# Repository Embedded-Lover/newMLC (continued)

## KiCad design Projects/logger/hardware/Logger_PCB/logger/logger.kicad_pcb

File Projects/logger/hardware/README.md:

# MLC_CAN_Logger_Hardware

## Getting started

To make it easy for you to get started with GitLab, here's a list of recommended next steps.

Already a pro? Just edit this README.md and make it your own. Want to make it easy? [Use the template at the bottom](#editing-this-readme)!

## Add your files

- [ ] [Create](https://docs.gitlab.com/ee/user/project/repository/web_editor.html#create-a-file) or [upload](https://docs.gitlab.com/ee/user/project/repository/web_editor.html#upload-a-file) files
- [ ] [Add files using the command line](https://docs.gitlab.com/ee/gitlab-basics/add-file.html#add-a-file-using-the-command-line) or push an existing Git repository with the following command:

```
cd existing_repo
git remote add origin https://git.mapnalocomotive.com/ahmadi_y/mlc_can_logger_hardware.git
git branch -M main
git push -uf origin main
```

## Integrate with your tools

- [ ] [Set up project integrations](https://git.mapnalocomotive.com/ahmadi_y/mlc_can_logger_hardware/-/settings/integrations)

## Collaborate with your team

- [ ] [Invite team members and collaborators](https://docs.gitlab.com/ee/user/project/members/)
- [ ] [Create a new merge request](https://docs.gitlab.com/ee/user/project/merge_requests/creating_merge_requests.html)
- [ ] [Automatically close issues from merge requests](https://docs.gitlab.com/ee/user/project/issues/managing_issues.html#closing-issues-automatically)
- [ ] [Enable merge request approvals](https://docs.gitlab.com/ee/user/project/merge_requests/approvals/)
- [ ] [Set auto-merge](https://docs.gitlab.com/ee/user/project/merge_requests/merge_when_pipeline_succeeds.html)

## Test and Deploy

Use the built-in continuous integration in GitLab.

- [ ] [Get started with GitLab CI/CD](https://docs.gitlab.com/ee/ci/quick_start/index.html)
- [ ] [Analyze your code for known vulnerabilities with Static Application Security Testing (SAST)](https://docs.gitlab.com/ee/user/application_security/sast/)
- [ ] [Deploy to Kubernetes, Amazon EC2, or Amazon ECS using Auto Deploy](https://docs.gitlab.com/ee/topics/autodevops/requirements.html)
- [ ] [Use pull-based deployments for improved Kubernetes management](https://docs.gitlab.com/ee/user/clusters/agent/)
- [ ] [Set up protected environments](https://docs.gitlab.com/ee/ci/environments/protected_environments.html)

***

# Editing this README

When you're ready to make this README your own, just edit this file and use the handy template below (or feel free to structure it however you want - this is just a starting point!). Thanks to [makeareadme.com](https://www.makeareadme.com/) for this template.

## Suggestions for a good README

Every project is different, so consider which of these sections apply to yours. The sections used in the template are suggestions for most open source projects. Also keep in mind that while a README can be too long and detailed, too long is better than too short. If you think your README is too long, consider utilizing another form of documentation rather than cutting out information.

## Name
Choose a self-explaining name for your project.

## Description
Let people know what your project can do specifically. Provide context and add a link to any reference visitors might be unfamiliar with. A list of Features or a Background subsection can also be added here. If there are alternatives to your project, this is a good place to list differentiating factors.

## Badges
On some READMEs, you may see small images that convey metadata, such as whether or not all the tests are passing for the project. You can use Shields to add some to your README. Many services also have instructions for adding a badge.

## Visuals
Depending on what you are making, it can be a good idea to include screenshots or even a video (you'll frequently see GIFs rather than actual videos). Tools like ttygif can help, but check out Asciinema for a more sophisticated method.

## Installation
Within a particular ecosystem, there may be a common way of installing things, such as using Yarn, NuGet, or Homebrew. However, consider the possibility that whoever is reading your README is a novice and would like more guidance. Listing specific steps helps remove ambiguity and gets people to using your project as quickly as possible. If it only runs in a specific context like a particular programming language version or operating system or has dependencies that have to be installed manually, also add a Requirements subsection.

## Usage
Use examples liberally, and show the expected output if you can. It's helpful to have inline the smallest example of usage that you can demonstrate, while providing links to more sophisticated examples if they are too long to reasonably include in the README.

## Support
Tell people where they can go to for help. It can be any combination of an issue tracker, a chat room, an email address, etc.

## Roadmap
If you have ideas for releases in the future, it is a good idea to list them in the README.

## Contributing
State if you are open to contributions and what your requirements are for accepting them.

For people who want to make changes to your project, it's helpful to have some documentation on how to get started. Perhaps there is a script that they should run or some environment variables that they need to set. Make these steps explicit. These instructions could also be useful to your future self.

You can also document commands to lint the code or run tests. These steps help to ensure high code quality and reduce the likelihood that the changes inadvertently break something. Having instructions for running tests is especially helpful if it requires external setup, such as starting a Selenium server for testing in a browser.

## Authors and acknowledgment
Show your appreciation to those who have contributed to the project.

## License
For open source projects, say how it is licensed.

## Project status
If you have run out of energy or time for your project, put a note at the top of the README saying that development has slowed down or stopped completely. Someone may choose to fork your project or volunteer to step in as a maintainer or owner, allowing your project to keep going. You can also make an explicit request for maintainers.

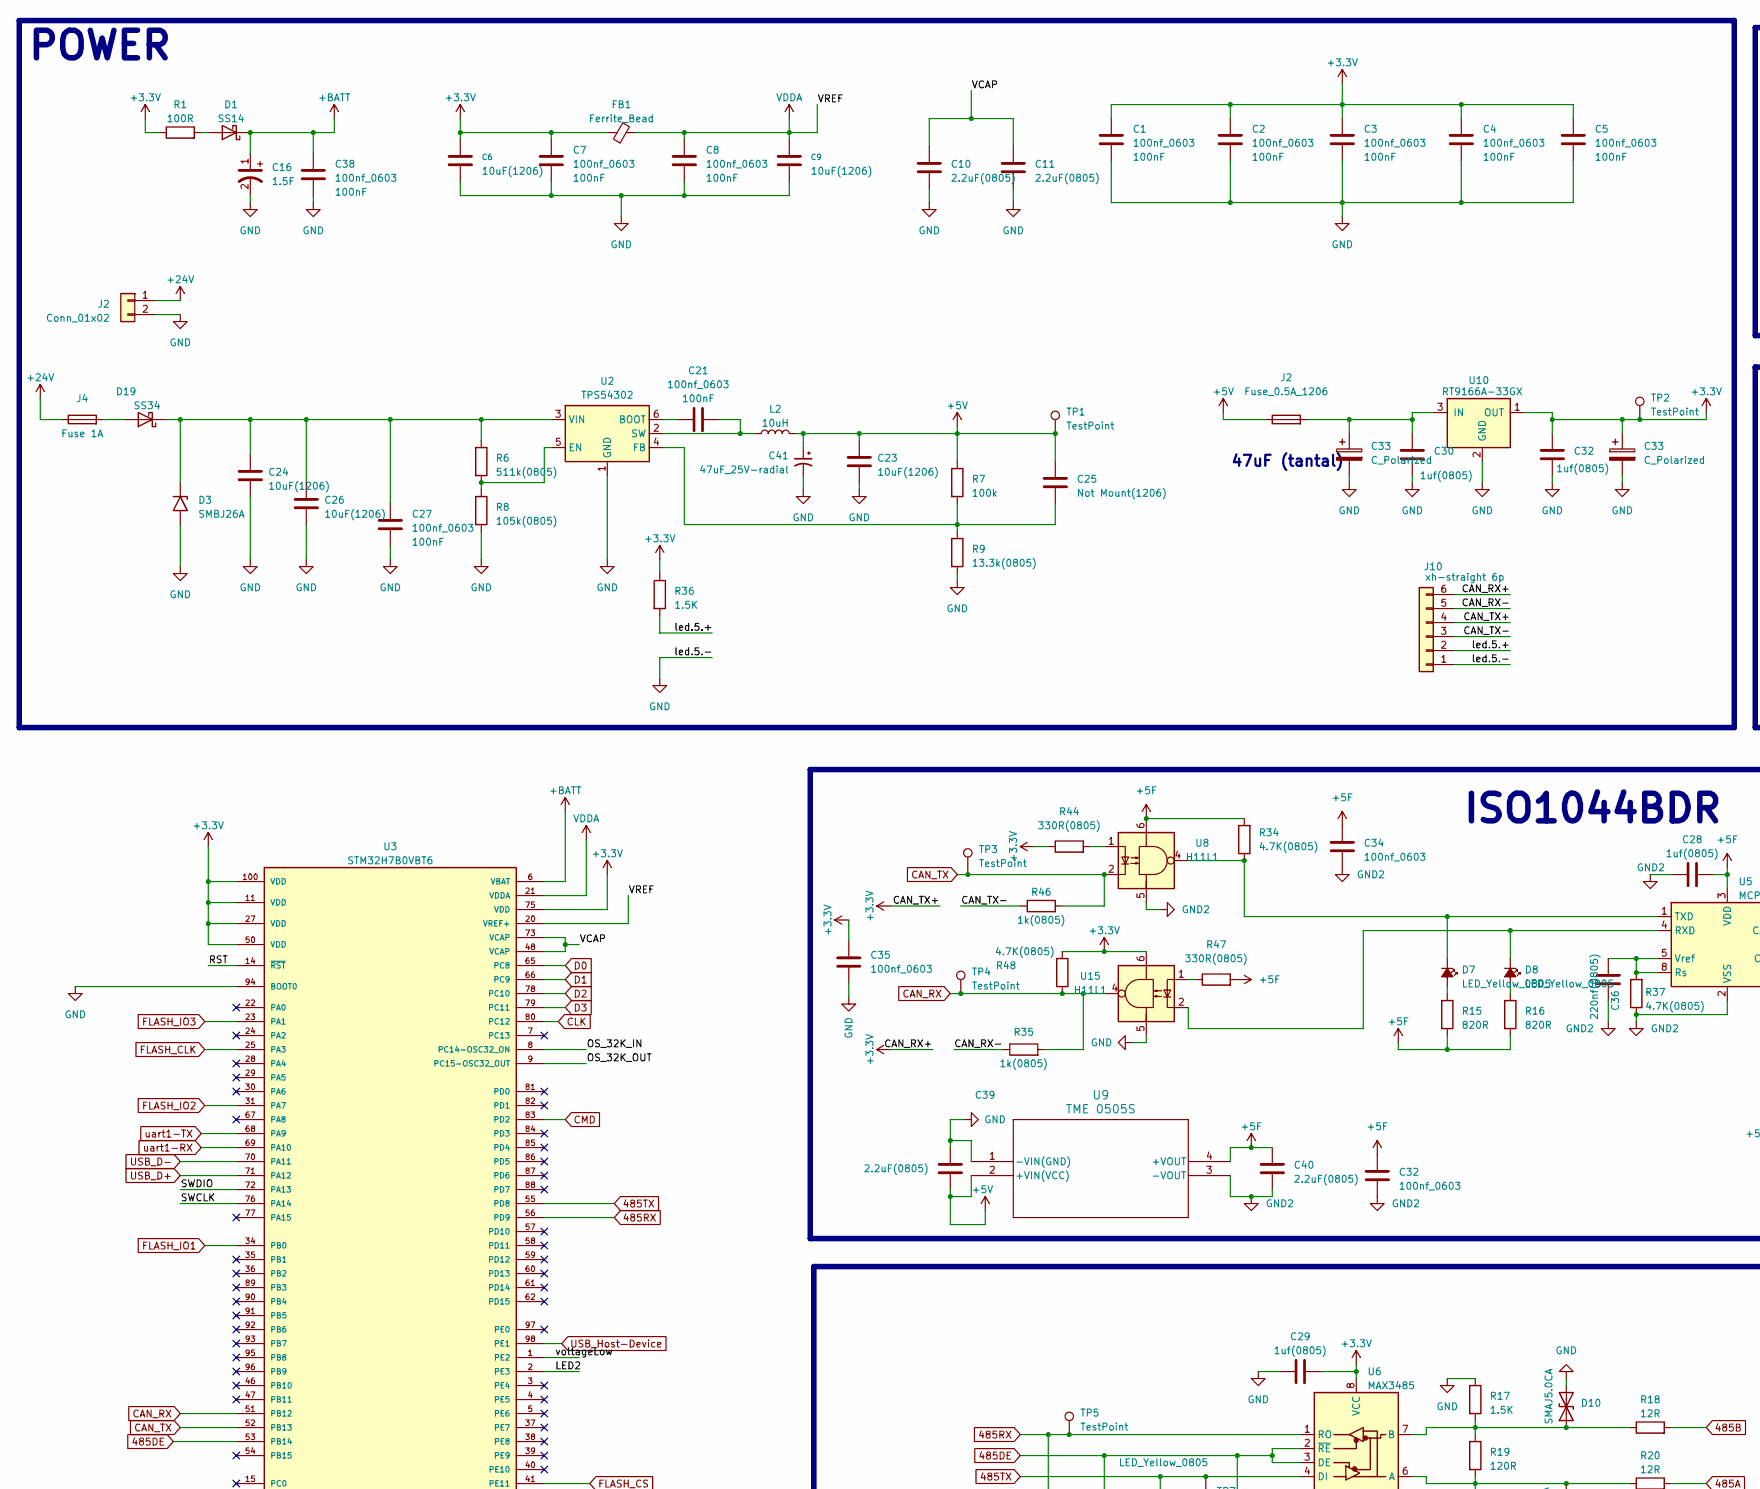
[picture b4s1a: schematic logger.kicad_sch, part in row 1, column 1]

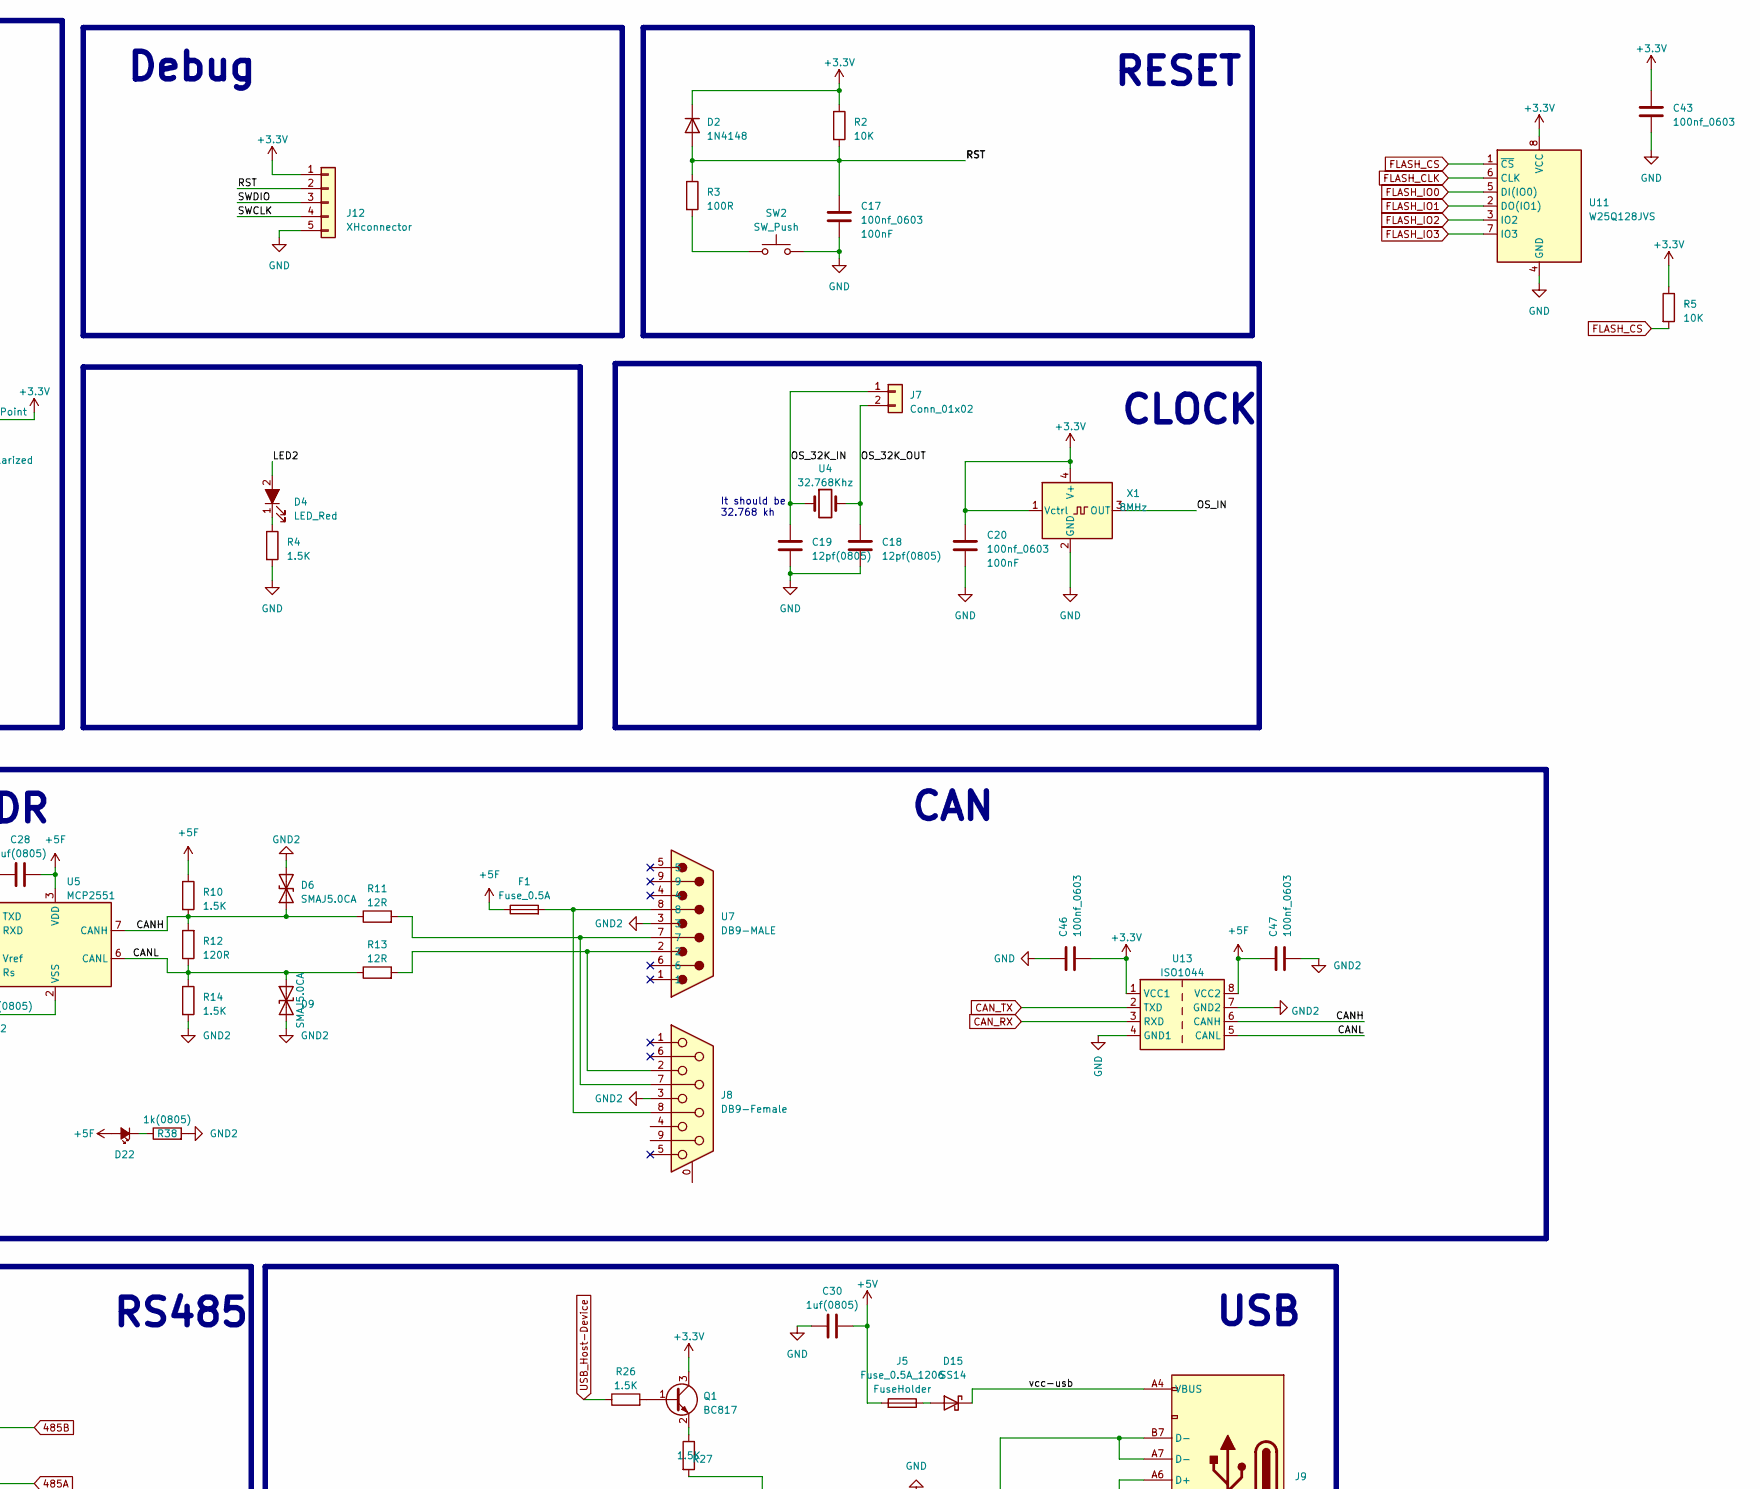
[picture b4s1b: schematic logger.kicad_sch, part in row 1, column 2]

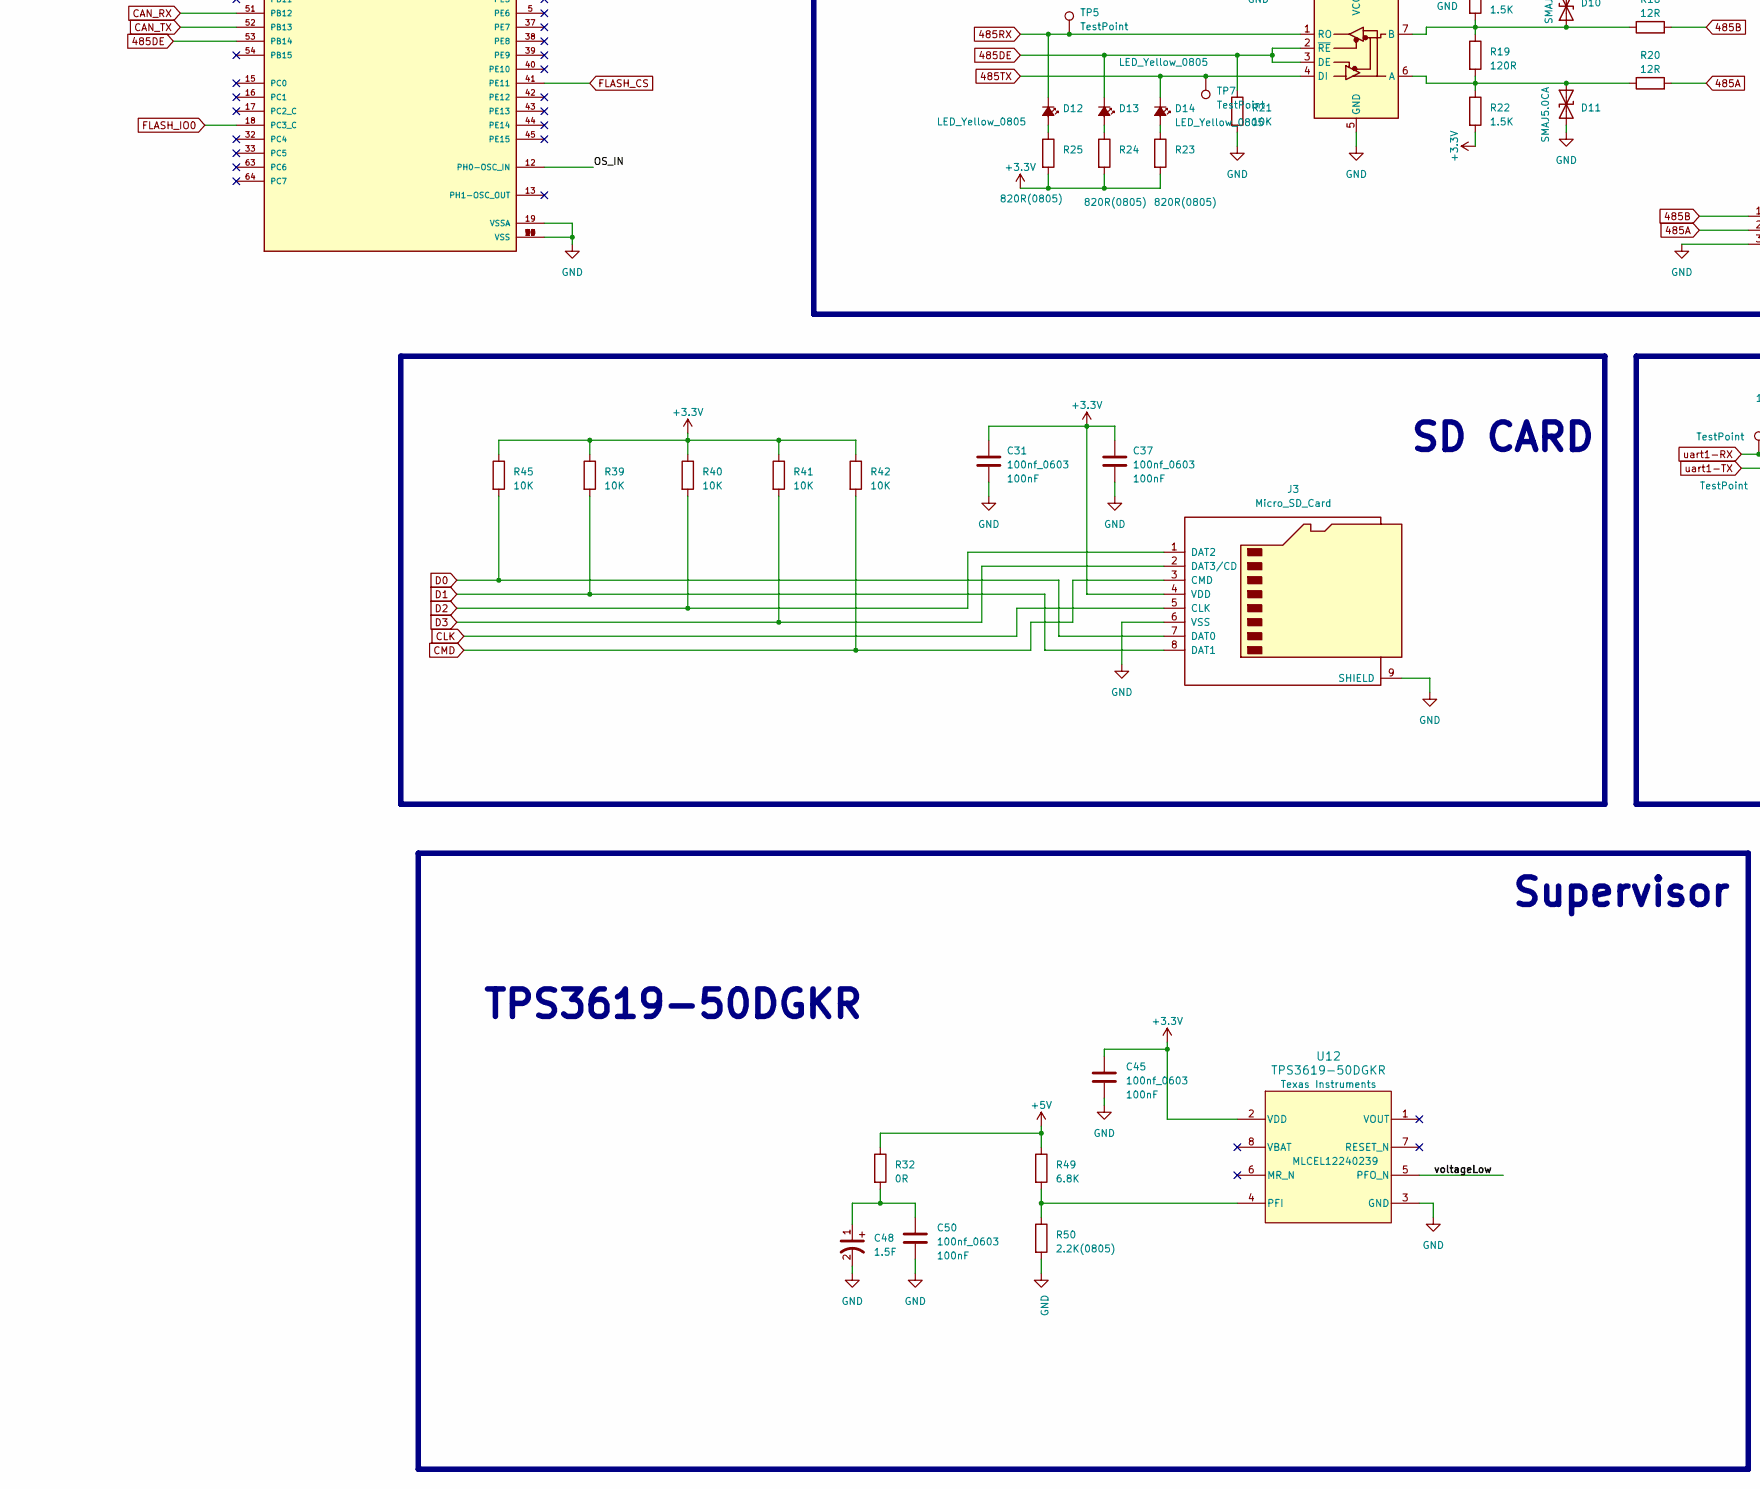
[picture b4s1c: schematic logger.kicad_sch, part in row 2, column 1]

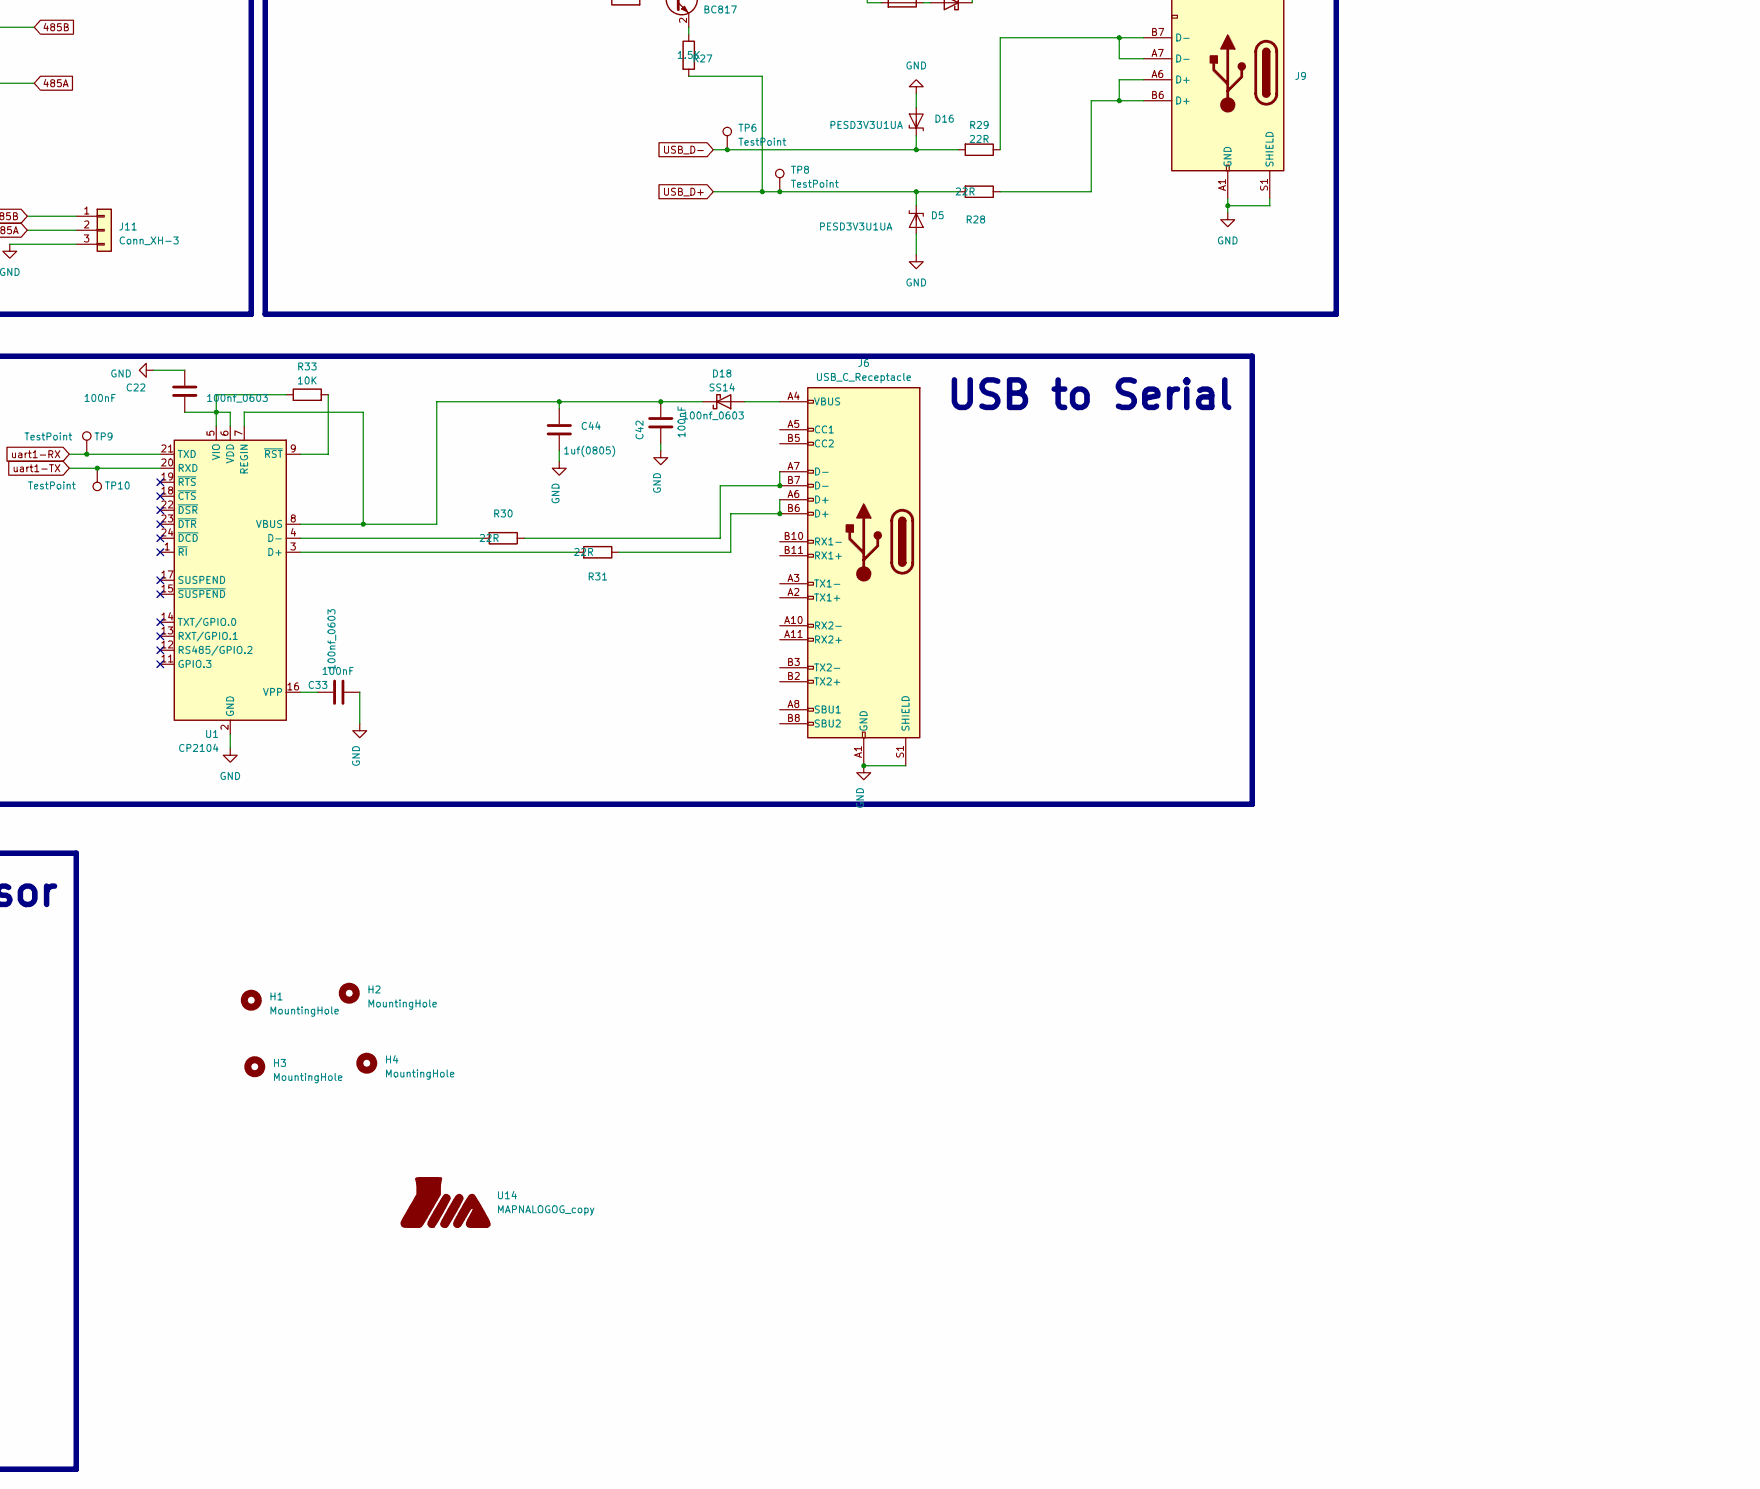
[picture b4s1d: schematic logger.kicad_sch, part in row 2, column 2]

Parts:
C1, C2, C3, C4, C5, C7, C8, C17, C20, C21, C22, C27, C31, C33, C37, C38, C42, C45, C50: 100nf_0603; C_0603_1608Metric_Pad1.08x0.95mm_HandSolder; MPN CGA4J2X7R1H104M125AE
C6, C9, C23, C24, C26: 10uF(1206); C_1206_3216Metric_Pad1.33x1.80mm_HandSolder; MPN CGA5L1X7R1H106K160AE
C10, C11, C39, C40: 2.2uF(0805); C_0805_2012Metric_Pad1.18x1.45mm_HandSolder; MPN C2012X7R2A225K125AC
C16: 1F-5.5v; super_cap_1.F-5.5V; MPN CEN5R5155VF-ZG
C18, C19: 12pf(0805); C_0805_2012Metric_Pad1.18x1.45mm_HandSolder
C25: Not Mount(1206); C_0805_2012Metric_Pad1.18x1.45mm_HandSolder
C28, C29, C30, C32, C44: 1uf(0805); C_0805_2012Metric_Pad1.15x1.40mm_HandSolder; MPN CGA4J3X7R1H105K125AE
C34, C35, C43, C46, C47: 100nf_0603; C_0603_1608Metric_Pad1.08x0.95mm_HandSolder
C36: 220nf(0805); C_0805_2012Metric_Pad1.18x1.45mm_HandSolder
C41: 47uF_25V-radial; CP_Radial_D5.0mm_P2.00mm; MPN EEUFC1E470
C48: 1F-5.5v; super cap; MPN CEN5R5155VF-ZG
D1, D15, D18: SS14; D_SMA; MPN SS14
D2: 1N4148_MiniMELF; D_MiniMELF; MPN LL4148
D3: SMBJ26A; D_SMB_Handsoldering
D4: LED_RED(0805)_FP K7; LED_0805_2012Metric_Pad1.15x1.40mm_HandSolder; MPN IN-S85CS5R
D5, D16: PESD3V3U1UA,115; D_SOD-323_HandSoldering; MPN PESD3V3U1UA,115
D6, D9, D10, D11: SMAJ5.0CA; D_SMA
D7, D8, D12, D13, D14: LED_Yellow_0805; LED_0805_2012Metric_Pad1.15x1.40mm_HandSolder; MPN 150080YS75000
D19: SS34-sma; D_SMA_Handsoldering; MPN SS34-HF
D22: LED_RED_0805; LED_0805_2012Metric_Pad1.15x1.40mm_HandSolder
F1: Fuse_0.5A; Fuse_1206_3216Metric_Pad1.42x1.75mm_HandSolder
FB1: Ferrite_Bead(1206); L_1206_3216Metric_Pad1.42x1.75mm_HandSolder; MPN CBG321609U102
H1, H2, H3, H4: MountingHole; MountingHole_3.5mm_Pad_Via
J2, J5: Fuse_0.5A_1206; Fuse_1206_3216Metric_Pad1.42x1.75mm_HandSolder; MPN 01550900M
J3: Micro_SD_Card; microSD_HC_Hirose_DM3AT-SF-PEJM5
J4: Fuse_1A_1206; Fuse_1206_3216Metric_Pad1.42x1.75mm_HandSolder; MPN JFC1206 1100FS 63V 1A
J6: USB_C_Receptacle; USB_C_Receptacle_G-Switch_GT-USB-7010ASV
J7: Conn_01x02; Crystal_C26-LF_D2.1mm_L6.5mm_Horizontal
J8: DB9-Female-right-pcb_mount; DSUB-9_Female_Horizontal_P2.77x2.84mm_EdgePinOffset7.70mm_H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; MPN DEMG9SJA197
J9: gt-usb
J10: xh-straight 6p; JST_XH_B6B-XH-AM_1x06_P2.50mm_Vertical
J11: Conn_XH-3-right; JST_XH_S3B-XH-A-1_1x03_P2.50mm_Horizontal
J12: XH-connector-straight-5P; JST_XH_B5B-XH-A_1x05_P2.50mm_Vertical; MPN B5B-XH-A
L2: 10uH; L_7.3x6.6_H3.5
Q1: BC817-smd; SOT-23W_Handsoldering; MPN BC817K-25R
R1, R3: 100R(0805); R_0805_2012Metric_Pad1.20x1.40mm_HandSolder; MPN RN73R2ATTD1000F25
R2, R5, R21, R33, R39, R40, R41, R42, R45: 10K(0805); R_0805_2012Metric_Pad1.20x1.40mm_HandSolder; MPN RN73R2ATTD1002F25
R4, R10, R14, R17, R22, R26, R27, R36: 1.5K(0805); R_0805_2012Metric_Pad1.20x1.40mm_HandSolder; MPN RN73R2ATTD1501F25
R6: 511k(0805); R_0805_2012Metric_Pad1.20x1.40mm_HandSolder
R7: 100k; R_0805_2012Metric_Pad1.15x1.40mm_HandSolder; MPN RN73R2ATTD1003B25
R8: 105k(0805); R_0805_2012Metric_Pad1.20x1.40mm_HandSolder
R9: 13.3k(0805); R_0805_2012Metric_Pad1.20x1.40mm_HandSolder
R11, R13, R18, R20: 12R(0805); R_0805_2012Metric_Pad1.15x1.40mm_HandSolder; MPN RN73R2A12R0F25
R12, R19: 120R(0805); R_0805_2012Metric_Pad1.20x1.40mm_HandSolder; MPN RN73R2ATTD1200F25
R15, R16: 820R(0805); R_0805_2012Metric_Pad1.20x1.40mm_HandSolder; MPN RN73R2ATTD8200F25
R23, R24, R25: 820R(0805); R_0805_2012Metric_Pad1.20x1.40mm_HandSolder
R28, R29, R30, R31: 22R(0805); R_0805_2012Metric_Pad1.20x1.40mm_HandSolder
R32: 0R(1206); R_1206_3216Metric_Pad1.30x1.75mm_HandSolder; MPN CRCW12060000Z0EB
R34, R37, R48: 4.7K(0805); R_0805_2012Metric_Pad1.20x1.40mm_HandSolder
R35, R38, R46: 1k(0805); R_0805_2012Metric_Pad1.20x1.40mm_HandSolder
R44, R47: 330R(0805); R_0805_2012Metric_Pad1.20x1.40mm_HandSolder
R49: 6.8K(0805); R_0805_2012Metric_Pad1.20x1.40mm_HandSolder; MPN RN73R2ATTD6801F25
R50: 2.2K(0805); R_0805_2012Metric_Pad1.20x1.40mm_HandSolder; MPN RK73G2ATTD2201D
SW2: SW_Push; SW_SPST_CK_RS282G05A3
TP1, TP2, TP3, TP4, TP5, TP6, TP7, TP8, TP9, TP10: TestPoint; TestPoint_THTPad_1.0x1.0mm_Drill0.5mm
U1: CP2104; QFN-24-1EP_4x4mm_P0.5mm_EP2.6x2.6mm
U2: TPS54302DDCR; SOT-23-6; MPN TPS54302DDCR
U3: STM32H7B0VBT6; LQFP-100_14x14mm_P0.5mm; MPN STM32H7B0VBT6
U4: Crystal-_32.768Khz-smd; Crystal_SMD_3215-2Pin_3.2x1.5mm; MPN ABS07-32.768KHZ-T
U5: MCP2551; SOIC-8_3.9x4.9mm_P1.27mm; MPN MCP2551T-E/SN
U6: MAX3485; SO-8_3.9x4.9mm_P1.27mm
U7: DB9-MALE; DSUB-9_Male_Horizontal_P2.77x2.84mm_EdgePinOffset7.70mm_Hou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
U8, U15: H11L1-SMD; SMDIP-6_W7.62mm; MPN H11L1SM
U9: TME 0505S; TME 3.3-5-12V_TRP
U10: RT9166A-33GX; SOT-89-3_Handsoldering
U11: W25Q128JVS; SOIC-8_5.23x5.23mm_P1.27mm
U12: TPS3619-50DGKR; VSSOP-8_3.0x3.0mm_P0.65mm; MPN TPS3619-50DGKR
U13: ISO1044; SOIC-8_3.9x4.9mm_P1.27mm; MPN ISO1044BDR
U14: MAPNALOGOG_copy; mapnal logo -s
X1: Ocs_8MHz; Oscillator_SMD_Fordahl_DFAS11-4Pin_7.0x5.0mm

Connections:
485A: J11.2, R20.2
485B: J11.1, R18.2
485DE: D13.1 (K), R21.1, U3.53 (PB14), U6.2 (~RE), U6.3 (DE)
485RX: D12.1 (K), TP5.1, U3.56 (PD9), U6.1 (RO)
485TX: D14.1 (K), TP7.1, U3.55 (PD8), U6.4 (DI)
+BATT: C16.1, C38.1, D1.1 (K), U3.6 (VBAT)
/CANH: D6.1 (A1), R10.2, R11.1, R12.2, U5.7 (CANH), U13.6 (CANH)
/CANL: D9.1 (A1), R12.1, R13.1, R14.1, U5.6 (CANL), U13.5 (CANL)
/CAN_RX-: J10.5, R35.1
/CAN_TX-: J10.3, R46.1
/LED2: D4.2 (A), U3.2 (PE3)
/OS_32K_IN: C19.1, J7.1, U3.8 (PC14-OSC32_ON), U4.1
/OS_32K_OUT: C18.1, J7.2, U3.9 (PC15-OSC32_OUT), U4.2
/OS_IN: U3.12 (PH0-OSC_IN), X1.3 (OUT)
/RST: C17.1, D2.2 (A), J12.2, R2.2, R3.1, U3.14 (~RST)
/SWCLK: J12.4, U3.76 (PA14)
/SWDIO: J12.3, U3.72 (PA13)
/VCAP: C10.1, C11.1, U3.48 (VCAP), U3.73 (VCAP)
/led.5.+: J10.2, R36.2
/vcc-usb: D15.1 (K), J9.A4 (VBUS), J9.A9 (VBUS), J9.B4 (VBUS), J9.B9 (VBUS)
/voltageLow: U3.1 (PE2), U12.5 (PFO_N)
CAN_RX: R35.2, R48.1, TP4.1, U3.51 (PB12), U13.3 (RXD), U15.4
CAN_TX: R46.2, TP3.1, U3.52 (PB13), U8.2, U13.2 (TXD)
CLK: J3.5 (CLK), U3.80 (PC12)
CMD: J3.3 (CMD), R42.2, U3.83 (PD2)
D0: J3.7 (DAT0), R45.2, U3.65 (PC8)
D1: J3.8 (DAT1), R39.2, U3.66 (PC9)
D2: J3.1 (DAT2), R40.2, U3.78 (PC10)
D3: J3.2 (DAT3/CD), R41.2, U3.79 (PC11)
FLASH_CLK: U3.25 (PA3), U11.6 (CLK)
FLASH_CS: R5.2, U3.41 (PE11), U11.1 (~CS)
FLASH_IO0: U3.18 (PC3_C), U11.5 (DI(IO0))
FLASH_IO1: U3.34 (PB0), U11.2 (DO(IO1))
FLASH_IO2: U3.31 (PA7), U11.3 (IO2)
FLASH_IO3: U3.23 (PA1), U11.7 (IO3)
unnamed: C48.1, C50.1, R32.2
unnamed: D1.2 (A), R1.2
unnamed: D4.1 (K), R4.1
unnamed: D7.2 (A), R15.1
unnamed: D7.1 (K), R34.1, U5.1 (TXD), U8.4
unnamed: D8.2 (A), R16.1
unnamed: D8.1 (K), U5.4 (RXD), U15.2
unnamed: D10.1 (A1), R17.2, R18.1, R19.1, U6.7 (B)
unnamed: D11.1 (A1), R19.2, R20.1, R22.1, U6.6 (A)
unnamed: D12.2 (A), R25.1
unnamed: D13.2 (A), R24.1
unnamed: D14.2 (A), R23.1
unnamed: D15.2 (A), J5.1
unnamed: D18.2 (A), J6.A4 (VBUS), J6.A9 (VBUS), J6.B4 (VBUS), J6.B9 (VBUS)
unnamed: C42.2, C44.1, D18.1 (K), U1.7 (REGIN), U1.8 (VBUS)
unnamed: D19.2 (A), J4.2
unnamed: C24.1, C26.1, C27.1, D3.1 (A1), D19.1 (K), R6.1, U2.3 (VIN)
unnamed: D22.1 (K), R38.1
unnamed: F1.2, J8.8, U7.8
unnamed: J6.A6 (D+), J6.B6 (D+), R31.1
unnamed: J6.A7 (D-), J6.B7 (D-), R30.1
unnamed: J8.2, R13.2, U7.2
unnamed: J8.7, R11.2, U7.7
unnamed: J9.A5 (CC), J9.B5 (VCONN)
unnamed: J9.A6 (D+), J9.B6 (D+), R28.1
unnamed: J9.A7 (D-), J9.B7 (D-), R29.1
unnamed: Q1.1 (B), R26.2
unnamed: Q1.2 (E), R27.1
unnamed: R3.2, SW2.1
unnamed: R44.2, U8.1
unnamed: R47.1, U15.1
unnamed: R31.2, U1.3 (D+)
unnamed: R30.2, U1.4 (D-)
unnamed: C22.2, R33.1, U1.5 (VIO), U1.6 (VDD)
unnamed: R33.2, U1.9 (~RST)
unnamed: C21.1, U2.6 (BOOT)
unnamed: R6.2, R8.1, U2.5 (EN)
unnamed: C25.2, R7.2, R9.1, U2.4 (FB)
unnamed: C21.2, L2.1, U2.2 (SW)
unnamed: C36.2, R37.2, U5.5 (Vref), U5.8 (Rs)
unnamed: R49.2, R50.1, U12.4 (PFI)
USB_D+: D5.1 (A1), R27.2, R28.2, TP8.1, U3.71 (PA12)
USB_D-: D16.1 (A1), R29.2, TP6.1, U3.70 (PA11)
USB_Host-Device: R26.1, U3.98 (PE1)
VDDA: C8.1, C9.1, FB1.2, U3.20 (VREF+), U3.21 (VDDA)
uart1-RX: TP9.1, U1.21 (TXD), U3.69 (PA10)
uart1-TX: TP10.1, U1.20 (RXD), U3.68 (PA9)

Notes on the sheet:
47uF (tantal)
TPS3619-50DGKR
SD CARD
RESET
POWER
Debug
CAN
RS485
CLOCK
USB
Supervisor
It should be 32.768 kh
ISO1044BDR
USB to Serial

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
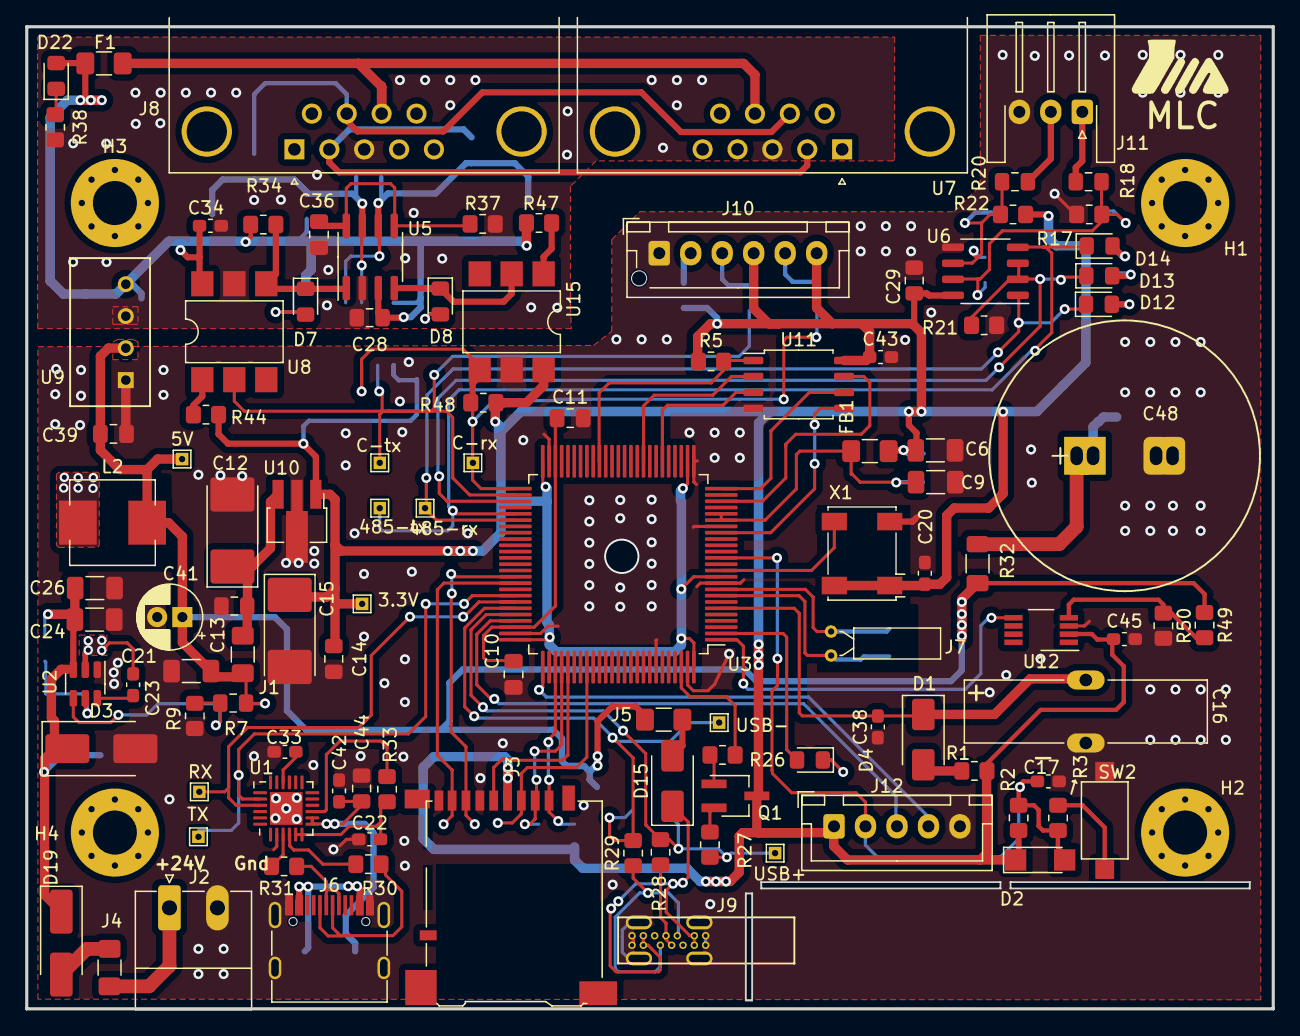
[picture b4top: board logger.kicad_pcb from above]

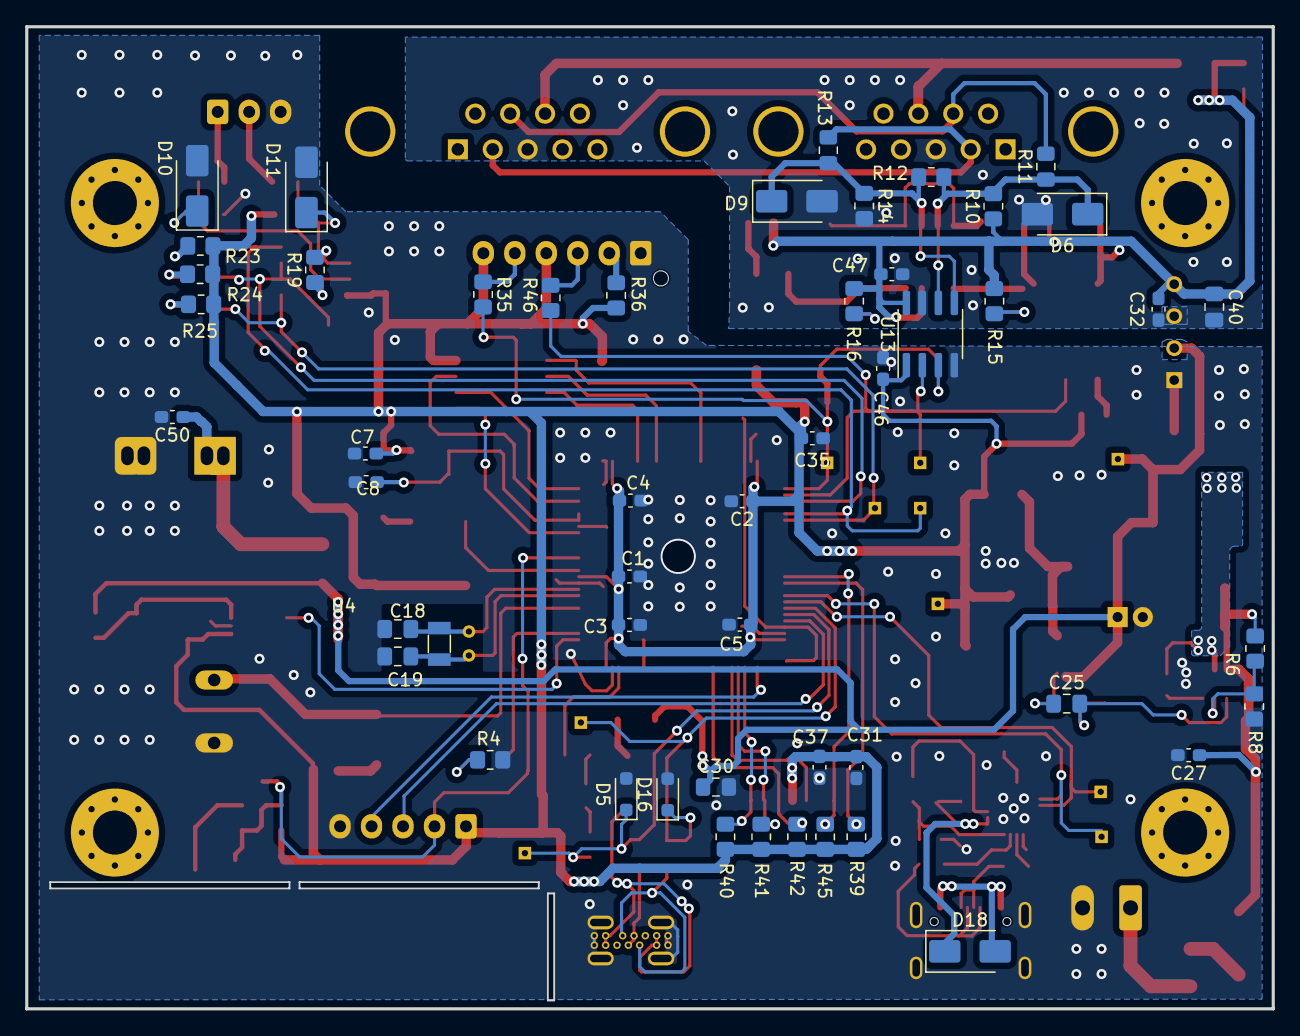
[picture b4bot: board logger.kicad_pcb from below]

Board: 2 copper layers, 99.0 x 78.0 mm, 164 parts (51 on the bottom side), 90 nets.

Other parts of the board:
C12, C15: C_Polarized; CP_EIA-7132-28_AVX-C_Pad2.72x3.50mm_HandSolder
C13, C14: 1uf(0805); C_0805_2012Metric_Pad1.15x1.40mm_HandSolder
J1: Fuse_0.5A_1206; Fuse_1206_3216Metric_Pad1.42x1.75mm_HandSolder

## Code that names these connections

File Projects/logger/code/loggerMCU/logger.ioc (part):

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Mcu.Name=STM32H7B0VBTx
Mcu.Package=LQFP100
Mcu.UserName=STM32H7B0VBTx
PA10.Mode=Asynchronous
PA10.Signal=LPUART1_RX
PA11.GPIOParameters=GPIO_Speed
PA11.GPIO_Speed=GPIO_SPEED_FREQ_LOW
PA11.Mode=Host_FS
PA11.Signal=USB_OTG_HS_DM
PA12.GPIOParameters=GPIO_Speed
PA12.GPIO_Speed=GPIO_SPEED_FREQ_LOW
PA12.Mode=Host_FS
PA12.Signal=USB_OTG_HS_DP
PA13.Mode=Serial_Wire
PA13.Signal=DEBUG_JTMS-SWDIO
PA14.Mode=Serial_Wire
PA14.Signal=DEBUG_JTCK-SWCLK
PA9.Mode=Asynchronous
PA9.Signal=LPUART1_TX
PB12.Mode=FDCAN_Activate
PB12.Signal=FDCAN2_RX
PB13.Mode=FDCAN_Activate
PB13.Signal=FDCAN2_TX
PC10.Mode=SD_4_bits_Wide_bus
PC10.Signal=SDMMC1_D2
PC11.Mode=SD_4_bits_Wide_bus
PC11.Signal=SDMMC1_D3
PC12.Mode=SD_4_bits_Wide_bus
PC12.Signal=SDMMC1_CK
PC14-OSC32_IN.Mode=LSE-External-Oscillator
PC14-OSC32_IN.Signal=RCC_OSC32_IN
PC15-OSC32_OUT.Mode=LSE-External-Oscillator
PC15-OSC32_OUT.Signal=RCC_OSC32_OUT
PC8.Mode=SD_4_bits_Wide_bus
PC8.Signal=SDMMC1_D0
PC9.Mode=SD_4_bits_Wide_bus
PC9.Signal=SDMMC1_D1
PD2.Mode=SD_4_bits_Wide_bus
PD2.Signal=SDMMC1_CMD
PE1.GPIOParameters=GPIO_Label
PE1.GPIO_Label=USB_Host_Device
PE1.Signal=GPIO_Output
PE2.GPIOParameters=GPIO_PuPd,GPIO_Label,GPIO_ModeDefaultEXTI
PE2.GPIO_Label=voltageLow
PE2.GPIO_ModeDefaultEXTI=GPIO_MODE_IT_RISING_FALLING
PE2.GPIO_PuPd=GPIO_NOPULL
PE2.Signal=GPXTI2
PE3.GPIOParameters=GPIO_Label
PE3.GPIO_Label=LED
PE3.Signal=GPIO_Output
PH0-OSC_IN.Mode=HSE-External-Oscillator
PH0-OSC_IN.Signal=RCC_OSC_IN
PH1-OSC_OUT.Mode=HSE-External-Oscillator
PH1-OSC_OUT.Signal=RCC_OSC_OUT
RCC.HSE_VALUE=16000000
RCC.SYSCLKFreq_VALUE=280000000
RCC.SYSCLKSource=RCC_SYSCLKSOURCE_PLLCLK
board=custom
